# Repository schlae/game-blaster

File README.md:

# Game Blaster (CT-1300)

Here's the partially reverse engineered Game Blaster/Creative Music System card. Some information is still missing, particularly for the ID chip, but also the values of a few capacitors. Some guesses were made about traces on the top layer hidden from view by chips or other components. That's right, this is based on a few photos of the card I was able to find.

This isn't a complete design. Don't expect to be able to fab it out and have a working card. I'm putting this up in the hopes that someone might find it a useful reference for further reverse engineering work.

[Schematic](https://github.com/schlae/game-blaster/blob/main/GameBlaster.pdf)

## Unknowns

Here's a list of everything that is not currently known about the card.

* Values of C14, C21, C22, the bodge capacitor on the back of the board, C23, C24, C25, C26, C27, C28, C36, zener diode Z1
* Traces on the top layer underneath IC4, IC8, and IC9 are mostly guesses
* The identity of the mystery chip, IC4.
* Differences between revision A and revision B.

## Mystery ID chip

### Identifiers

This chip is a 40-pin DIP marked as follows:

```
8827
CT 1302 A
CTPL 8708
```

```
CT1302A
CTPL8708
28840HA05
```

```
CT1302A
CTPL8708
28844HA05
```

Some cards have a chip that has been sanded down and labeled with a plain paper sticker:

```
C.M.S.
CT1302
```

If we believe the markings, we might assume that this is an OTP gate array device or potentially a mask-programmed gate array. "CTPL" might stand for "Creative Technology Programmable Logic" and "8708" might refer to the year 1987 and the work week 8, which implies that this is when Creative released the data files to the company who manufactured the chip.

The remaining lines on the chip, "28844HA05" or "28840HA05" or "8827" seem to imply several different manufacture dates for the chips, all in 1988, work weeks 27, 40, and 44.

Of course, since chip markings are easily customizable, this might all be designed to throw competitors off the trail, and it's an off-the-shelf device that has been repurposed.

### Functionality

The chip provides several different functions:

* 8-bit data bus connection (bidirectional). This is wired directly to the ISA data bus.
* Two 8-bit ports. One each is wired to the SAA1099 sound generator chips. Each port has a control line that seems to be used to latch data into the port from the ISA data bus.
* Card ID register. When writing port 226h or reading port 22Ah, external logic selects some sort of internal 8-bit latch in the chip. Basic on the connections of AND gate IC8D, this latch may be shared with port B, which implies that the values latched in each port can be read back.
* Some type of shift register. It is not known if the shift register is coming from one of the existing port registers or is standalone. This is accessed by reading from port 224h and examining bit 7 (the MSB). Plenty of software assumes this is always 7Fh, but the CMSDRV.COM driver program checks for a pattern of 1s and 0s on the MSB when performing 8 consecutive read operations from this port.

### Partial Pin Description

| Pin | Direction | Description |
|-----|-----------|-------------|
| 1   |           | Gnd         |
| 2   | Input, active low | Latches the data bus on port A |
| 3-10 | Output   | Port A, output only? |
| 11 | Input, active low | Latches the data bus on port B |
| 12-19 | Output  | Port B, output only? |
| 20 | | VCC |
| 21 | | Gnd |
| 22 | Input | Unknown, strapped to VCC. Chip select? |
| 23 | Input | Unknown, strapped to VCC. Chip select? |
| 24, 25 | Inputs, active low | One could be a R\/W# line and the other a register select. | 
| 26 | Output | Unknown, output of a shift register? |
| 27 | Input, active low | Unknown, asserted to read the contents of port B |
| 28 | Input, active low | Unknown, asserted to reset the shift register? |
| 29 | Input, active low | Selects the shift register for access, or perhaps acts as the shift clock for the shift register |
| 30, 31 | | Unknown, likely no connect pins |
| 32-39 | Bidirectional | Connection to ISA data bus |
| 40 | | VCC

### CMSDRV.COM Code

I've reverse engineered parts of the CMS driver provided with the card, and learned a few things.

* The program performs a partial checksum of itself, writes the value out to the card ID register, and reads it back later on. The value is expected to be A0h.
* The program attempts to disguise the results of card detection by "encrypting" the card not detected string. The string is just XORed with 07h.
* The program uses self-modifying code in a few places, presumably to hamper reverse engineering efforts. Typically it just overwrites literal values that are part of MOV instructions. This is used to change the INT 21h from a 4Ch command (exit) to a 31h command (terminate and stay resident).
* After initializing the SAA1099 registers, the program reads from 224h eight times and checks bit 7. the first four values are ignored, but the last four must match the pattern `1100`.
* Right before terminating (and staying resident) the program stores a magic number at 228h.

## Next Steps

We need someone who has a card to examine it and provide photos from different angles so we can read the values of a bunch of the capacitors. Photos at extreme angles next to the column of chips on the left side of the board could help us follow the top layer traces. As an alternative, someone with a multimeter/continuity tester could help by measuring a few points to confirm connectivity.

Learning more about the mystery ID chip has a few paths forward:
* Someone out there may recognize the chip from the partial pinout
* Connect a logic analyzer to every pin of the chip, start CMSDRV.COM, and observe the waveforms
* Desolder the chip and experiment with unused functionality (strapped pins, unconnected pins, and so on)
* Destructively decapping the chip would be the simplest, but I doubt anyone would want to sacrifice a card for that. :)

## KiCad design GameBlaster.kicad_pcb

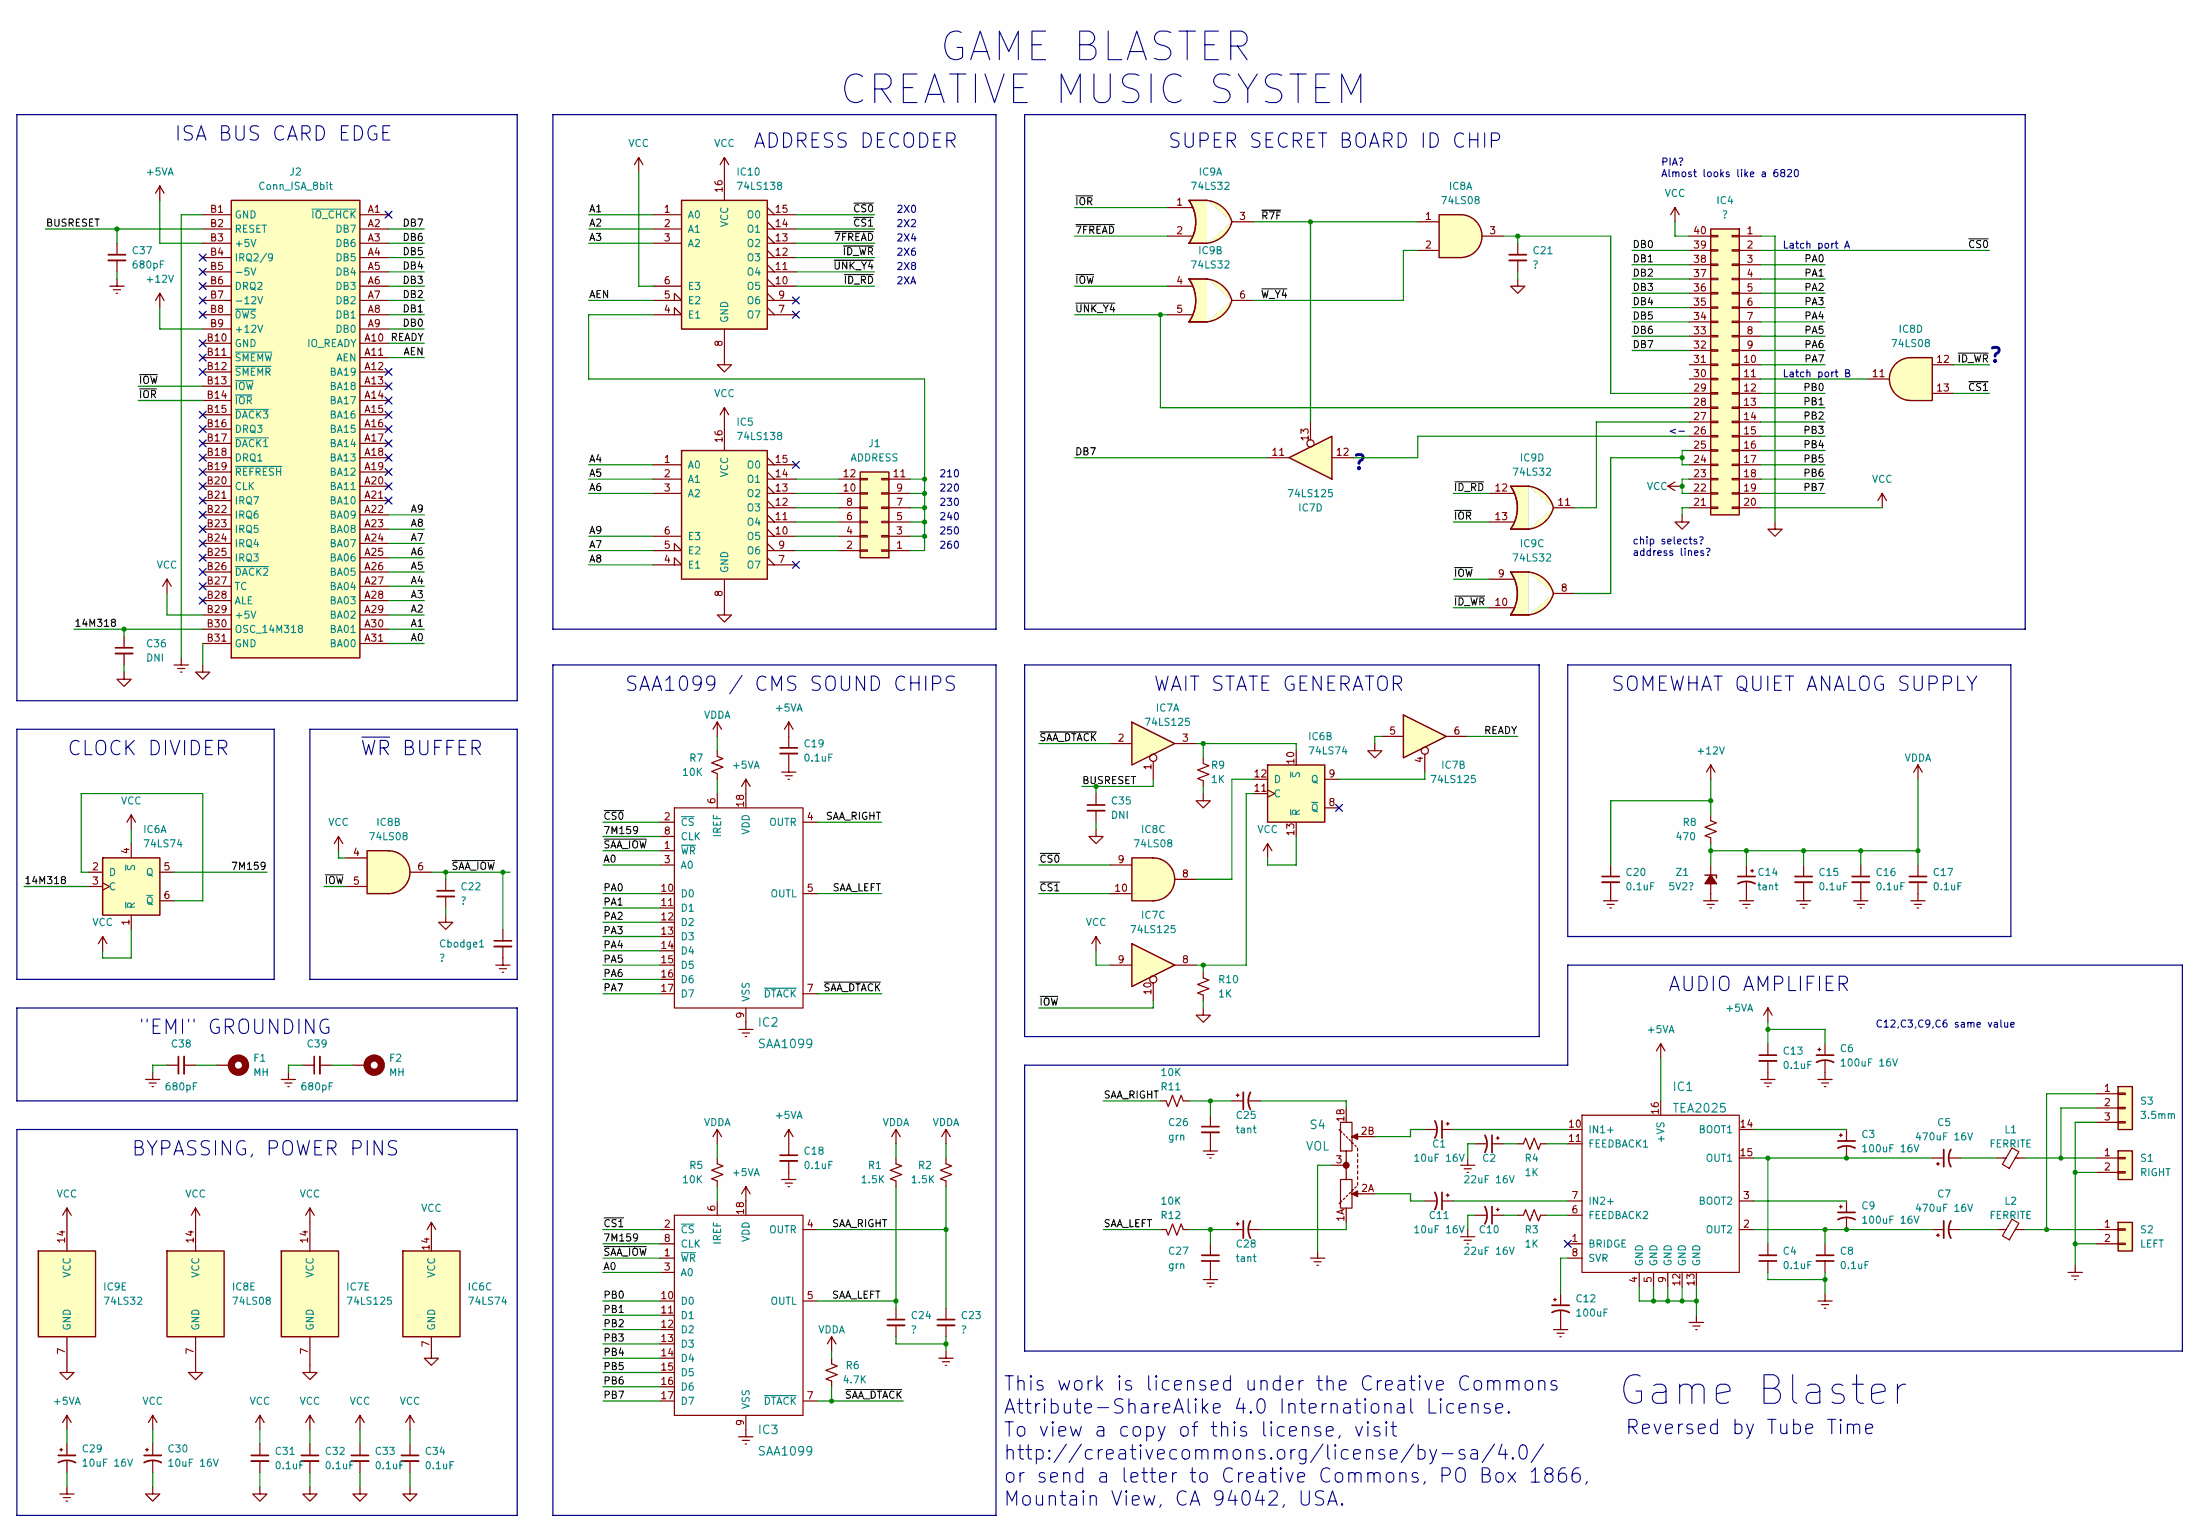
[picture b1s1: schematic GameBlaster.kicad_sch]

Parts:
C1, C11, C29, C30: 10uF 16V; CAPAP100
C2, C10: 22uF 16V; CAPAP100
C3, C6, C9: 100uF 16V; CAPAP100
C4, C8, C13, C15, C16, C17, C18, C19, C20, C31, C32, C33, C34: 0.1uF; CAPAC200
C5, C7: 470uF 16V; CAPAP200
C12: 100uF; CAPAP100
C14, C25, C28: tant; CAPAP100
C21, C22, C23, C24: ?; CAPAC200
C26, C27: grn; CAPAC200
C35, C36: DNI; CAPAC200
C37, C38, C39: 680pF; CAPAC200
Cbodge1: ?
F1, F2: MH; SB_MH_125
IC1: TEA2025; DIP254P762X635-16
IC2, IC3: SAA1099; DIP254P762X635-18
IC4: ?; DIP254P1524X635-40
IC5, IC10: 74LS138; DIP254P762X635-16
IC6: 74LS74; DIP254P762X635-14
IC7: 74LS125; DIP254P762X635-14
IC8: 74LS08; DIP254P762X635-14
IC9: 74LS32; DIP254P762X635-14
J1: ADDRESS; SB_HDR_2X6
J2: Conn_ISA_8bit; BUS_PC_8BIT
L1, L2: FERRITE; INDA500P780X750
R1, R2: 1.5K; RESA400
R3, R4, R9, R10: 1K; RESA400
R5, R7, R11, R12: 10K; RESA400
R6: 4.7K; RESA400
R8: 470; RESA400
S1: RIGHT; RCA_KYCON_KLPX
S2: LEFT; RCA_KYCON_KLPX
S3: 3.5mm; SJ1-3553NG
S4: VOL; SB_ALPS_RK08_DUAL
Z1: 5V2?; DIOA400

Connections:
+5VA: C6.1, C13.1, C18.1, C19.1, C29.1, IC1.16 (+VS), IC2.18 (VDD), IC3.18 (VDD), J2.B3 (+5V)
+12V: C20.1, J2.B9 (+12V), R8.1
/7M159: IC2.8 (CLK), IC3.8 (CLK), IC6.5 (Q)
/14M318: C36.1, IC6.3 (C), J2.B30 (OSC_14M318)
/A0: IC2.3 (A0), IC3.3 (A0), J2.A31 (BA00)
/A1: IC10.1 (A0), J2.A30 (BA01)
/A2: IC10.2 (A1), J2.A29 (BA02)
/A3: IC10.3 (A2), J2.A28 (BA03)
/A4: IC5.1 (A0), J2.A27 (BA04)
/A5: IC5.2 (A1), J2.A26 (BA05)
/A6: IC5.3 (A2), J2.A25 (BA06)
/A7: IC5.5 (E2), J2.A24 (BA07)
/A8: IC5.4 (E1), J2.A23 (BA08)
/A9: IC5.6 (E3), J2.A22 (BA09)
/AEN: IC10.5 (E2), J2.A11 (AEN)
/BUSRESET: C35.1, C37.1, IC7.1, J2.B2 (RESET)
/DB0: IC4.39, J2.A9 (DB0)
/DB1: IC4.38, J2.A8 (DB1)
/DB2: IC4.37, J2.A7 (DB2)
/DB3: IC4.36, J2.A6 (DB3)
/DB4: IC4.35, J2.A5 (DB4)
/DB5: IC4.34, J2.A4 (DB5)
/DB6: IC4.33, J2.A3 (DB6)
/DB7: IC4.32, IC7.11, J2.A2 (DB7)
/PA0: IC2.10 (D0), IC4.3
/PA1: IC2.11 (D1), IC4.4
/PA2: IC2.12 (D2), IC4.5
/PA3: IC2.13 (D3), IC4.6
/PA4: IC2.14 (D4), IC4.7
/PA5: IC2.15 (D5), IC4.8
/PA6: IC2.16 (D6), IC4.9
/PA7: IC2.17 (D7), IC4.10
/PB0: IC3.10 (D0), IC4.12
/PB1: IC3.11 (D1), IC4.13
/PB2: IC3.12 (D2), IC4.14
/PB3: IC3.13 (D3), IC4.15
/PB4: IC3.14 (D4), IC4.16
/PB5: IC3.15 (D5), IC4.17
/PB6: IC3.16 (D6), IC4.18
/PB7: IC3.17 (D7), IC4.19
/READY: IC7.6, J2.A10 (IO_READY)
/SAA_LEFT: C24.1, IC2.5 (OUTL), IC3.5 (OUTL), R1.2, R12.1
/SAA_RIGHT: C23.1, IC2.4 (OUTR), IC3.4 (OUTR), R2.2, R11.1
/~7FREAD: IC9.2, IC10.13 (O2)
/~CS0: IC2.2 (~CS), IC4.2, IC8.9, IC10.15 (O0)
/~CS1: IC3.2 (~CS), IC8.10, IC8.13, IC10.14 (O1)
/~ID_RD: IC9.12, IC10.10 (O5)
/~ID_WR: IC8.12, IC9.10, IC10.12 (O3)
/~IOR: IC9.1, IC9.13, J2.B14 (~IOR)
/~IOW: IC7.10, IC8.5, IC9.4, IC9.9, J2.B13 (~IOW)
/~R7F: IC7.13, IC8.1, IC9.3
/~SAA_DTACK: IC2.7 (~DTACK), IC3.7 (~DTACK), IC7.2, R6.1
/~SAA_IOW: C22.1, Cbodge1.1, IC2.1 (~WR), IC3.1 (~WR), IC8.6
/~UNK_Y4: IC4.28, IC9.5, IC10.11 (O4)
/~W_Y4: IC8.2, IC9.6
GND: C21.2, C22.2, C30.2, C31.2, C32.2, C33.2, C34.2, C35.2, C36.2, IC4.1, IC4.21, IC5.8 (GND), IC6.7 (GND), IC7.5, IC7.7 (GND), IC8.7 (GND), IC9.7 (GND), IC10.8 (GND), J2.B31 (GND), R9.2, R10.2
GNDREF: C2.2, C4.2, C6.2, C8.2, C10.2, C12.2, C13.2, C14.2, C15.2, C16.2, C17.2, C18.2, C19.2, C20.2, C23.2, C24.2, C26.2, C27.2, C29.2, C37.2, C38.1, C39.1, Cbodge1.2, IC1.4 (GND), IC1.5 (GND), IC1.9 (GND), IC1.12 (GND), IC1.13 (GND), IC2.9 (VSS), IC3.9 (VSS), J2.B1 (GND), S1.2, S2.2, S3.3, S4.3, Z1.2 (A)
unnamed: C1.1, IC1.10 (IN1+)
unnamed: C1.2, S4.2B
unnamed: C2.1, R4.1
unnamed: C3.1, IC1.14 (BOOT1)
unnamed: C3.2, C4.1, C5.1, IC1.15 (OUT1)
unnamed: C5.2, L1.1
unnamed: C7.1, C8.1, C9.2, IC1.2 (OUT2)
unnamed: C7.2, L2.1
unnamed: C9.1, IC1.3 (BOOT2)
unnamed: C10.1, R3.1
unnamed: C11.1, IC1.7 (IN2+)
unnamed: C11.2, S4.2A
unnamed: C12.1, IC1.8 (SVR)
unnamed: C21.1, IC4.29, IC8.3
unnamed: C27.1, C28.1, R12.2
unnamed: C28.2, S4.1A
unnamed: C25.1, C26.1, R11.2
unnamed: C25.2, S4.1B
unnamed: C38.2, F1.1
unnamed: C39.2, F2.1
unnamed: IC1.6 (FEEDBACK2), R3.2
unnamed: IC1.11 (FEEDBACK1), R4.2
unnamed: IC2.6 (IREF), R7.2
unnamed: IC3.6 (IREF), R5.2
unnamed: IC4.11, IC8.11
unnamed: IC4.24, IC4.25, IC9.8
unnamed: IC4.26, IC7.12
unnamed: IC4.27, IC9.11
unnamed: IC5.9 (O6), J1.2
unnamed: IC5.10 (O5), J1.4
unnamed: IC5.11 (O4), J1.6
unnamed: IC5.12 (O3), J1.8
unnamed: IC5.13 (O2), J1.10
unnamed: IC5.14 (O1), J1.12
unnamed: IC6.2 (D), IC6.6 (~Q)
unnamed: IC6.9 (Q), IC7.4
unnamed: IC6.10 (~S), IC7.3, R9.1
unnamed: IC6.11 (C), IC7.8, R10.1
unnamed: IC6.12 (D), IC8.8
unnamed: IC10.4 (E1), J1.1, J1.3, J1.5, J1.7, J1.9, J1.11
unnamed: L1.2, S1.1, S3.2
unnamed: L2.2, S2.1, S3.1
VCC: C30.1, C31.1, C32.1, C33.1, C34.1, IC4.20, IC4.22, IC4.23, IC4.40, IC5.16 (VCC), IC6.1 (~R), IC6.4 (~S), IC6.13 (~R), IC6.14 (VCC), IC7.9, IC7.14 (VCC), IC8.4, IC8.14 (VCC), IC9.14 (VCC), IC10.6 (E3), IC10.16 (VCC), J2.B29 (+5V)
VDDA: C14.1, C15.1, C16.1, C17.1, R1.1, R2.1, R5.1, R6.2, R7.1, R8.2, Z1.1 (K)

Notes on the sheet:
CREATIVE MUSIC SYSTEM
250
Reversed by Tube Time
~{WR} BUFFER
Latch port A
2X4
PIA? Almost looks like a 6820
ADDRESS DECODER
AUDIO AMPLIFIER
"EMI" GROUNDING
CLOCK DIVIDER
C12,C3,C9,C6 same value
2X6
Latch port B
2X8
230
2X2
SUPER SECRET BOARD ID CHIP
BYPASSING, POWER PINS
240
220
Game Blaster
2X0
WAIT STATE GENERATOR
210
260
GAME BLASTER
SAA1099 / CMS SOUND CHIPS
2XA
chip selects? address lines?
This work is licensed under the Creative Commons Attribute-ShareAlike 4.0 International License. To view a copy of this license, visit http://creativecommons.org/license/by-sa/4.0/ or send a letter to Creative Commons, PO Box 1866, Mountain View, CA 94042, USA.
SOMEWHAT QUIET ANALOG SUPPLY
ISA BUS CARD EDGE

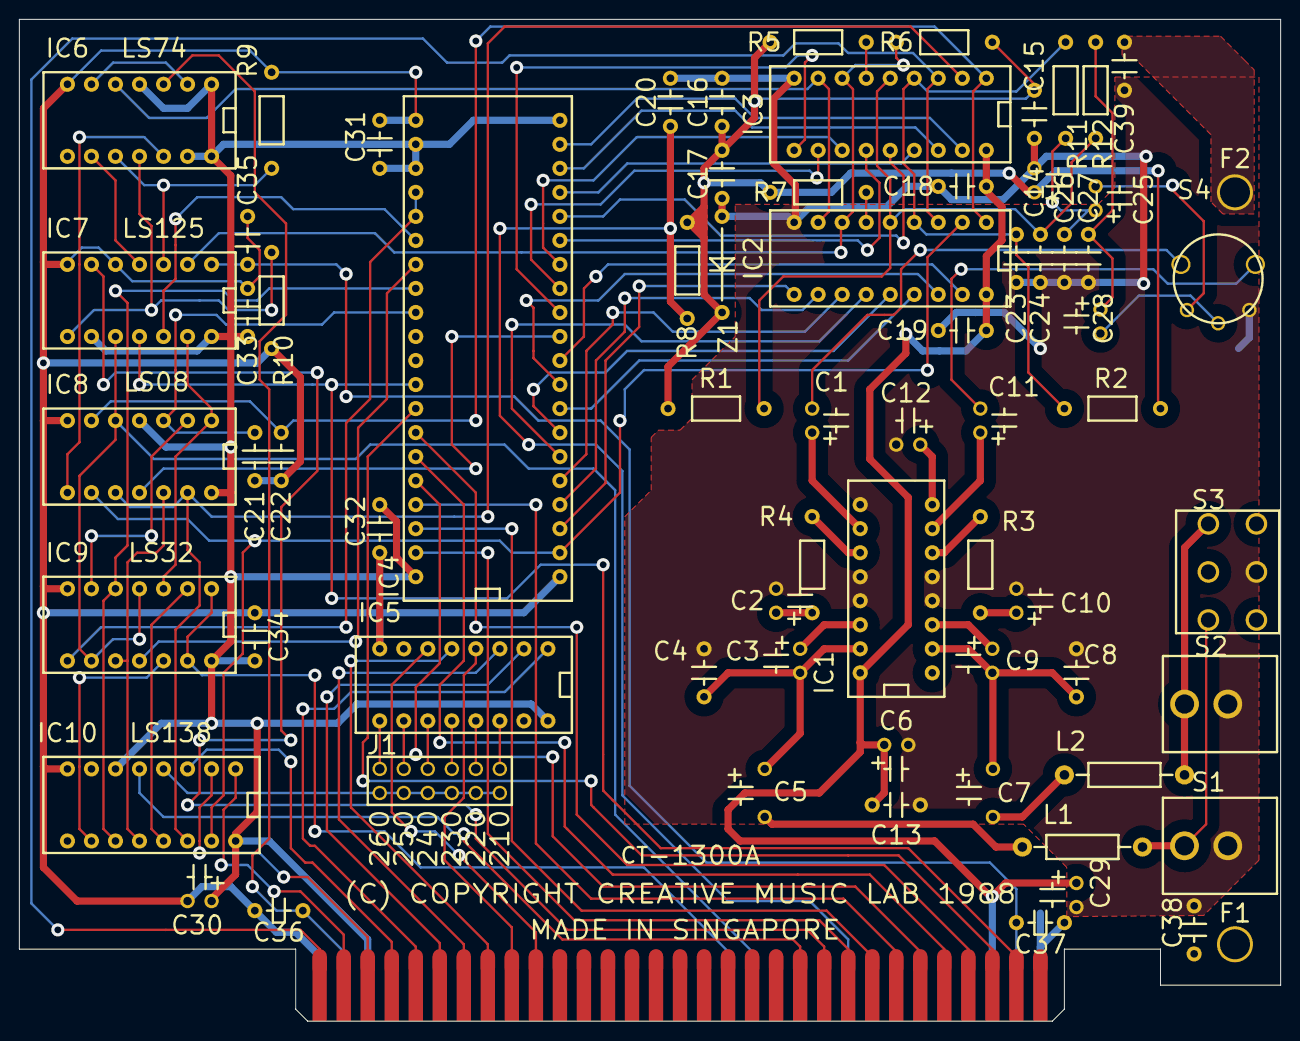
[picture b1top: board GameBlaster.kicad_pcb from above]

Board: 2 copper layers, 133.4 x 105.9 mm, 72 parts (0 on the bottom side), 101 nets.

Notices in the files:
GameBlaster.kicad_pcb:
(C) COPYRIGHT CREATIVE MUSIC LAB 1988
